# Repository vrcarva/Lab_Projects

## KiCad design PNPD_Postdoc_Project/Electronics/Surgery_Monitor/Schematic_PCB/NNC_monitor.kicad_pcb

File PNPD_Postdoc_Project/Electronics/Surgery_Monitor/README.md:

# Surgery Monitor
   
Project for monitoring heart rate and rectal temperature during surgery. In addition, the rectal temperature will be used as a control for the thermal blanket heating.
   
NNC / UFMG - since November 2018   

UPDATES:   

-----   

Add temperature code - 18/12/18 - 22:45

-----

Fixed interrupt for Temperature / Pulse measurement timer - 28/12/18 - 10:40 . 

-----

Add 5V RELAY for temperature control - 18/01/19 - 7:00 . 

--------------------------------------------------------------------------------

PULSE SENSOR:

References:

Guides:

   https://www.hackster.io/104829/detecting-heart-rate-with-a-photoresistor-680b58
   https://github.com/WorldFamousElectronics/PulseSensor_Amped_Arduino 
   https://makezine.com/projects/ir-pulse-sensor/
   https://www.instructables.com/id/Heart-rate-measuring-device-using-arduino/

Guide for default code:
Pulse Sensor Amped 1.5    by Joel Murphy and Yury Gitman  
  
   http://www.pulsesensor.com
   https://github.com/WorldFamousElectronics/PulseSensor_Amped_Arduino

Notes:
This code:
1) INPUT SIGNAL ANALOG PIN 0
2) Blinks an LED to User's Live Heartbeat   PIN 13
2) Fades an LED to User's Live HeartBeat    PIN 5
3) Determines BPM
4) Prints All of the Above to Serial

-----------------------------------------------------------------------------------------------------------

TEMPERATURE:

Original Articles:

   https://learn.adafruit.com/thermistor/using-a-thermistor

Other Guides:

   http://www.resistorguide.com/ntc-thermistor/
   https://en.wikipedia.org/wiki/Thermistor

Resistance at 25 degrees C --> // https://www.ametherm.com/blog/thermistor/arduino-and-thermistors

I have 2 kinds of Thermistors: 

- THERMISTOR NTC from TR-200 Temperaturregler Fine Science Tools - resistence 2252 ohm (25 C)
- THERMISTOR NTC 100K (25 C) from Filipe Flop store (Im using this one): 

   https://www.filipeflop.com/produto/termistor-ntc-100k-com-cabo/

Notes:
This code:
1) INPUT SIGNAL ANALOG PIN 1

--------------------------------------------------------------------------------

5V RELAY for temperature control

References:

Guides:
        
   http://www.circuitbasics.com/setting-up-a-5v-relay-on-the-arduino/
        
Notes:
This code:
1) OUTPUT SIGNAL DIGITAL PIN 2

--------------------------------------------------------------------------------
OLED DISPLAY:

Guides:
     
   https://startingelectronics.org/tutorials/arduino/modules/OLED-128x64-I2C-display/
   http://www.xtronical.com/pulseheartsensor/
   https://cdn-shop.adafruit.com/datasheets/SSD1306.pdf
   http://www.solomon-systech.com/files/ck/files/catalog/SSLcatalog_AD_OLED_Driver_IC_201604.pdf
   https://learn.adafruit.com/adafruit-gfx-graphics-library

Notes:
This code:

Arduino Uno/2009:

Display:  
SDA pin   -> Arduino Analog 4 or the dedicated SDA pin .     
SCL pin   -> Arduino Analog 5 or the dedicated SCL pin .

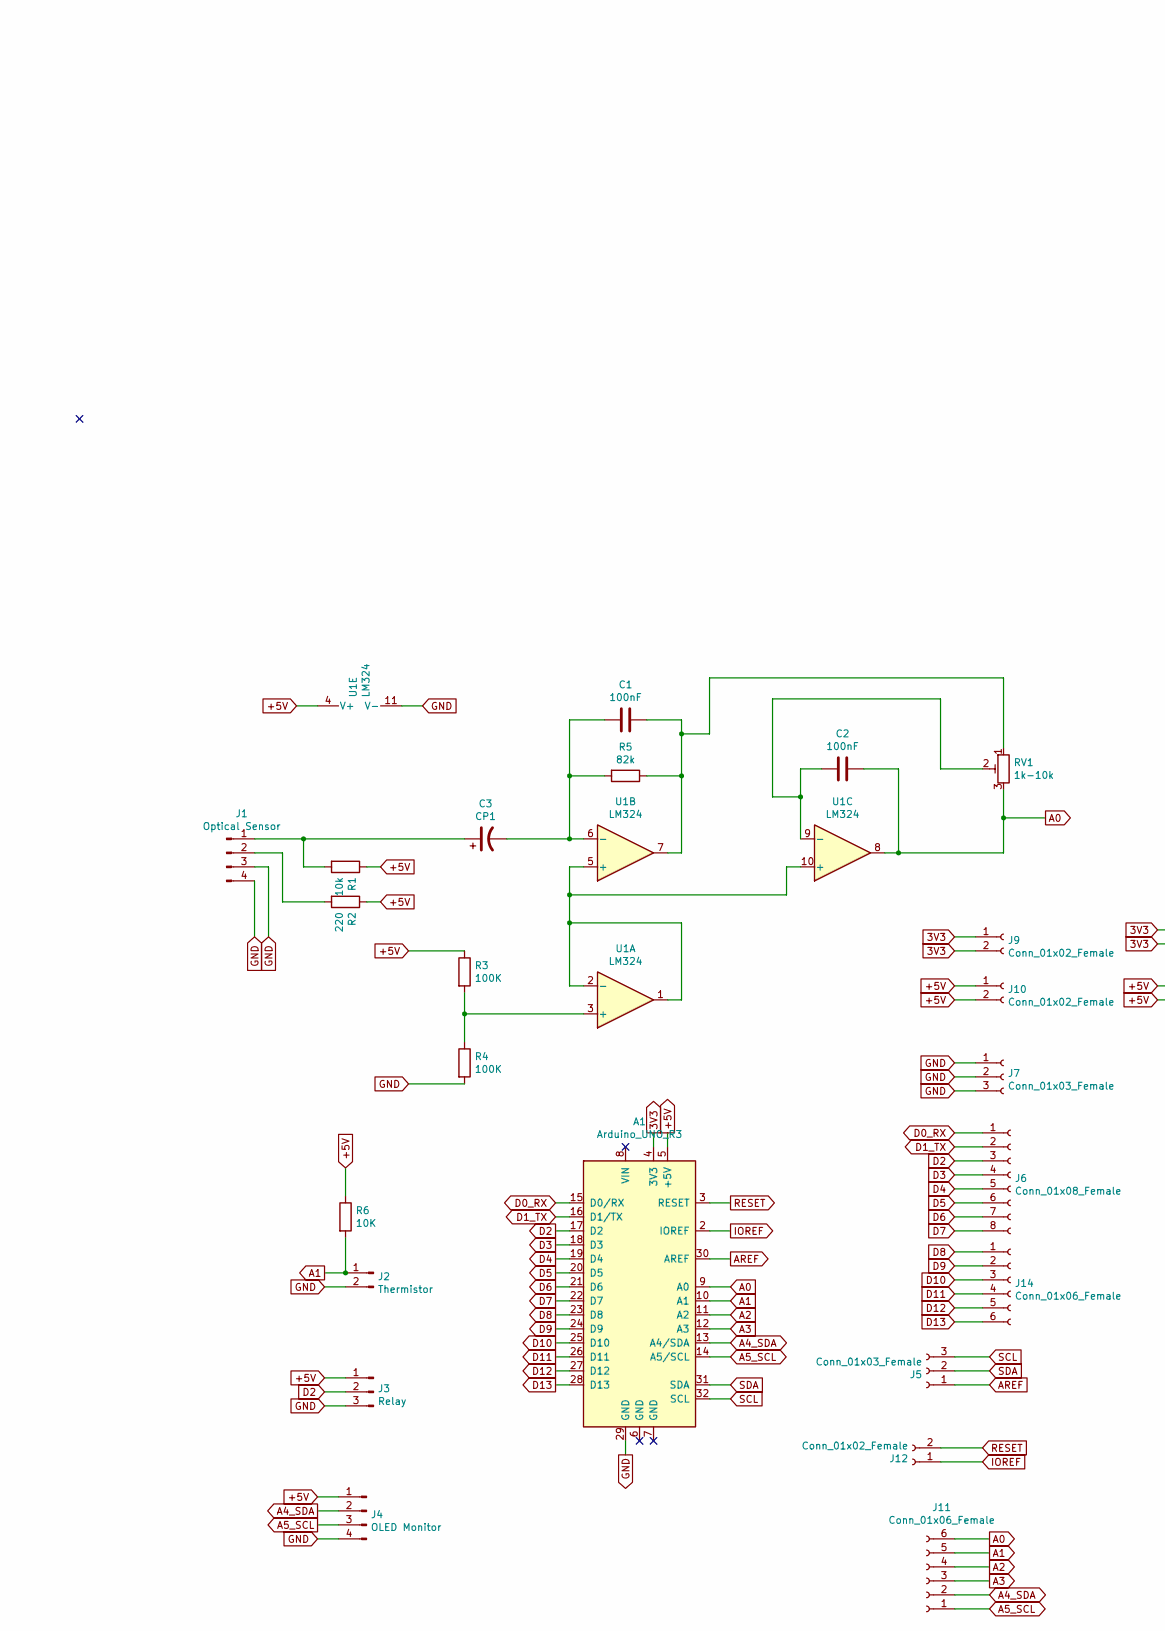
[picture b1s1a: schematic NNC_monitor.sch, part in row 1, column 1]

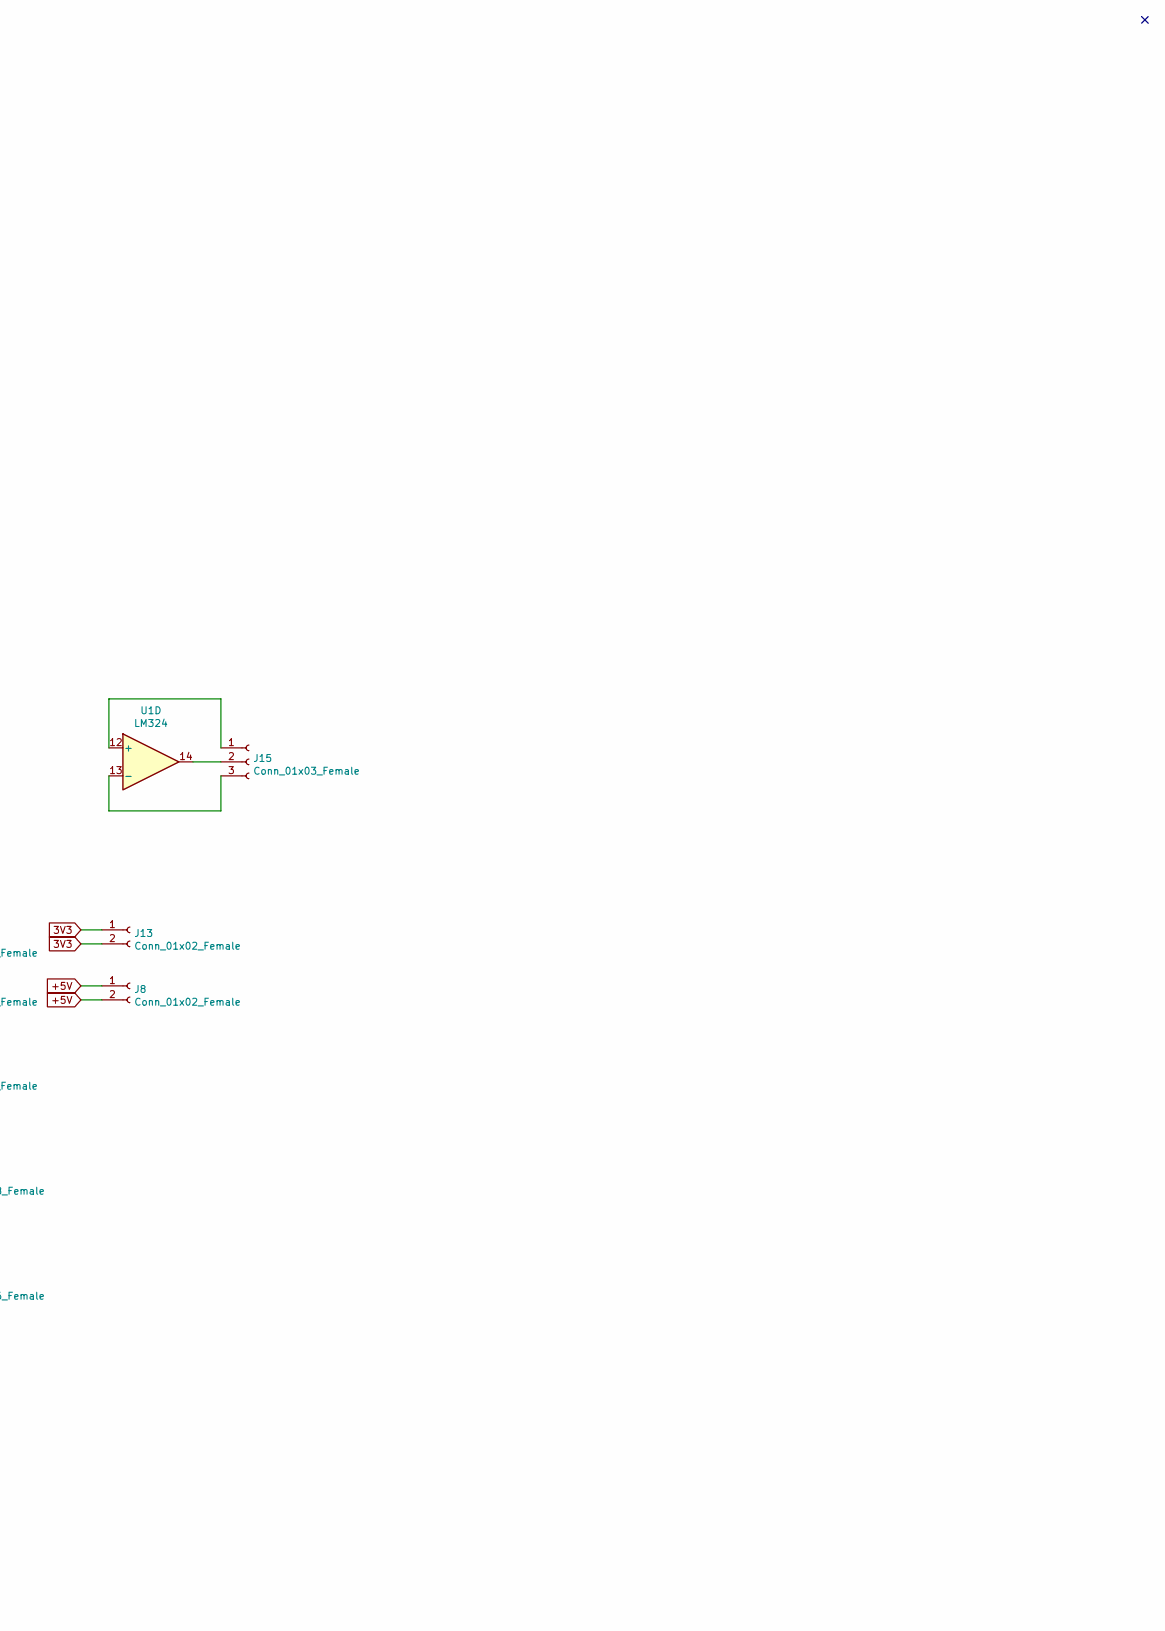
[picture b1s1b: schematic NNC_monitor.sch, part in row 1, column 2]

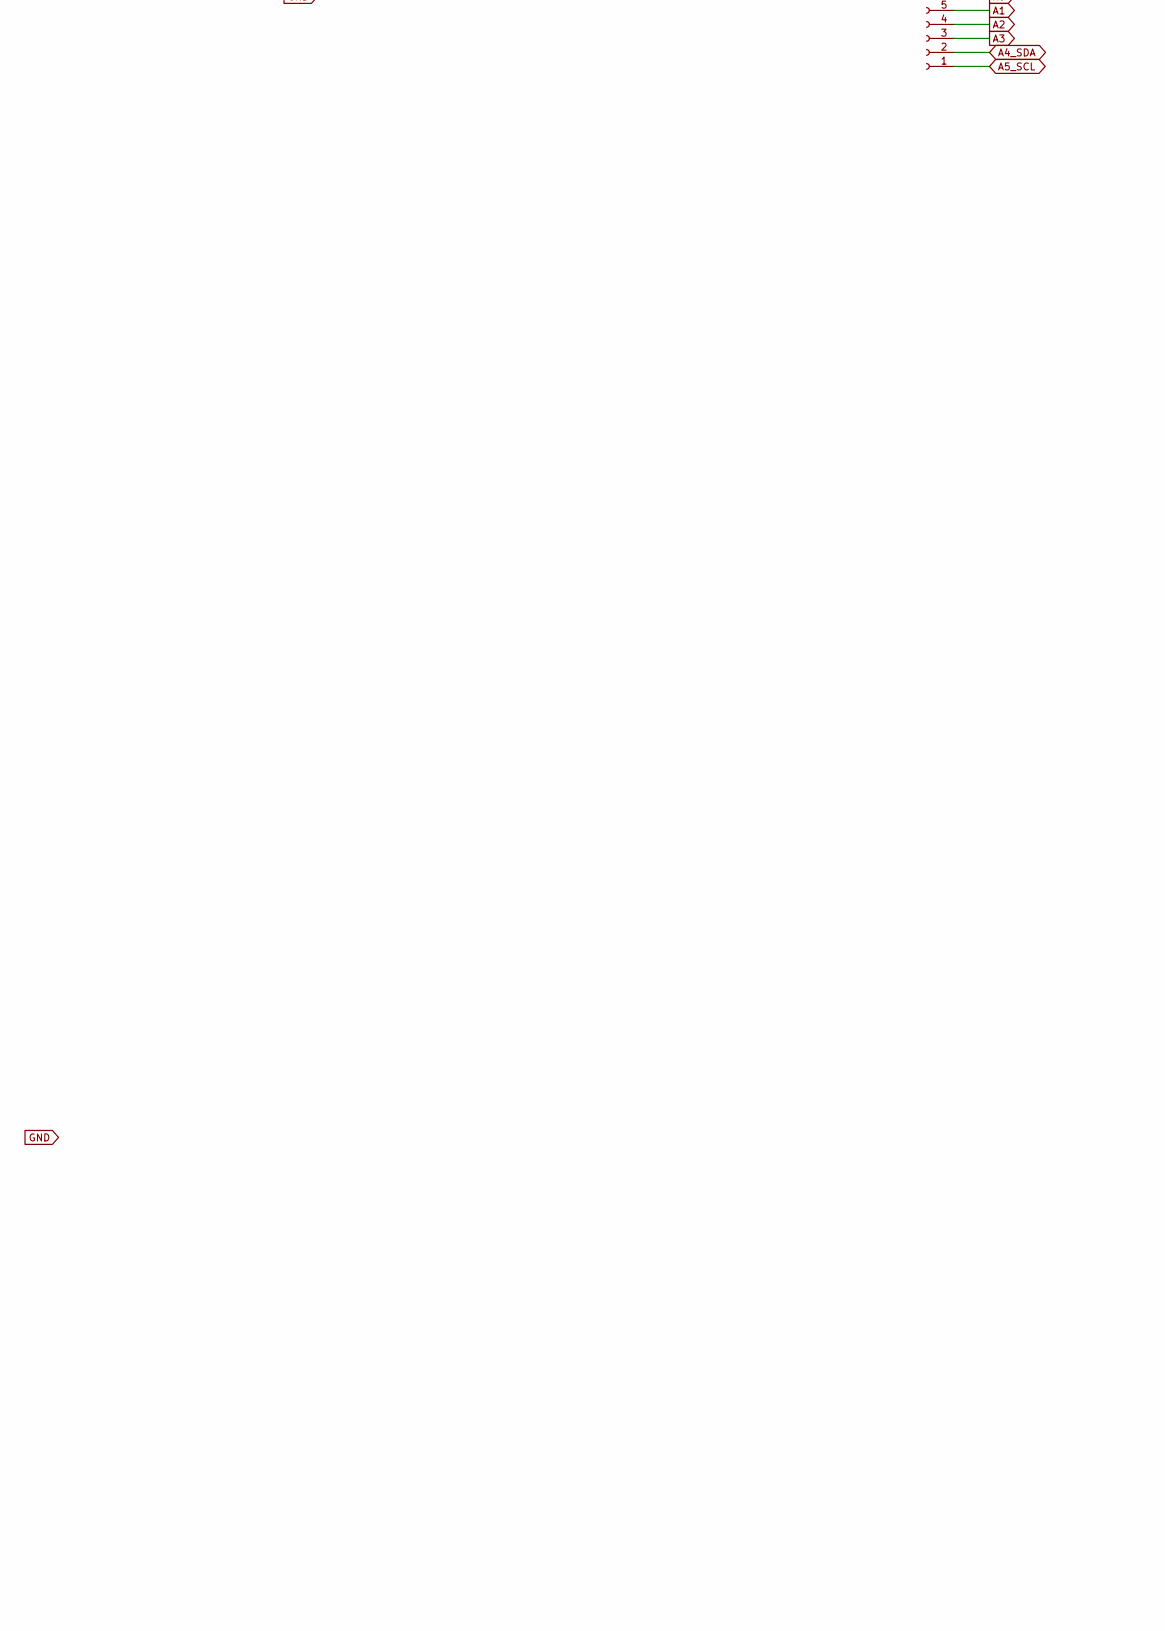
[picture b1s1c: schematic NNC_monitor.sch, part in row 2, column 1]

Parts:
A1: Arduino_UNO_R3
C1, C2: 100nF; C_Disc_D3_P2.5
C3: CP1; C_Radial_D5_L6_P2.5
J1: Optical Sensor; Molex_KK-254_AE-6410-04A_1x04_P2.54mm_Vertical
J2: Thermistor; Molex_KK-254_AE-6410-02A_1x02_P2.54mm_Vertical
J3: Relay; Molex_KK-254_AE-6410-03A_1x03_P2.54mm_Vertical
J4: OLED Monitor; Molex_KK-254_AE-6410-04A_1x04_P2.54mm_Vertical
J5, J7, J15: Conn_01x03_Female; PinSocket_1x03_P2.54mm_Vertical
J6: Conn_01x08_Female; PinSocket_1x08_P2.54mm_Vertical
J8, J9, J10, J12, J13: Conn_01x02_Female; PinSocket_1x02_P2.54mm_Vertical
J11, J14: Conn_01x06_Female; PinSocket_1x06_P2.54mm_Vertical
R1: 10k; Resistor_Horizontal_RM10mm
R2: 220; Resistor_Horizontal_RM10mm
R3, R4: 100K; Resistor_Horizontal_RM10mm
R5: 82k; Resistor_Horizontal_RM10mm
R6: 10K; Resistor_Horizontal_RM10mm
RV1: 1k-10k; Potentiometer_Trimmer-Suntan-TSR-3386P
U1: LM324; DIP-14_W7.62mm

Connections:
3V3: A1.4 (3V3), J9.1, J9.2, J13.1, J13.2
+5V: A1.5 (+5V), J3.1, J4.1, J8.1, J8.2, J10.1, J10.2, R1.1, R2.1, R3.1, R6.1, U1.4 (V+); also elsewhere on the board
A0: A1.9 (A0), C2.1, J11.6, RV1.3, U1.8
A1: A1.10 (A1), J2.1, J11.5, R6.2
A2: A1.11 (A2), J11.4
A3: A1.12 (A3), J11.3
A4_SDA: A1.13 (A4/SDA), J4.2, J11.2
A5_SCL: A1.14 (A5/SCL), J4.3, J11.1
AREF: A1.30 (AREF), J5.1
D0_RX: A1.15 (D0/RX), J6.1
D1_TX: A1.16 (D1/TX), J6.2
D2: A1.17 (D2), J3.2, J6.3
D3: A1.18 (D3), J6.4
D4: A1.19 (D4), J6.5
D5: A1.20 (D5), J6.6
D6: A1.21 (D6), J6.7
D7: A1.22 (D7), J6.8
D8: A1.23 (D8), J14.1
D9: A1.24 (D9), J14.2
D10: A1.25 (D10), J14.3
D11: A1.26 (D11), J14.4
D12: A1.27 (D12), J14.5
D13: A1.28 (D13), J14.6
GND: A1.29 (GND), J1.3, J1.4, J2.2, J3.3, J4.4, J7.1, J7.2, J7.3, R4.2, U1.11 (V-)
IOREF: A1.2 (IOREF), J12.1
unnamed: C1.1, R5.1, RV1.1, U1.7
unnamed: C1.2, C3.2, R5.2, U1.6 (-)
unnamed: C2.2, RV1.2, U1.9 (-)
unnamed: C3.1, J1.1, R1.2
unnamed: J1.2, R2.2
unnamed: J15.1, U1.12 (+)
unnamed: J15.2, U1.14
unnamed: J15.3, U1.13 (-)
unnamed: R3.2, R4.1, U1.3 (+)
unnamed: U1.1, U1.2 (-), U1.5 (+), U1.10 (+)
RESET: A1.3 (RESET), J12.2
SCL: A1.32 (SCL), J5.3
SDA: A1.31 (SDA), J5.2

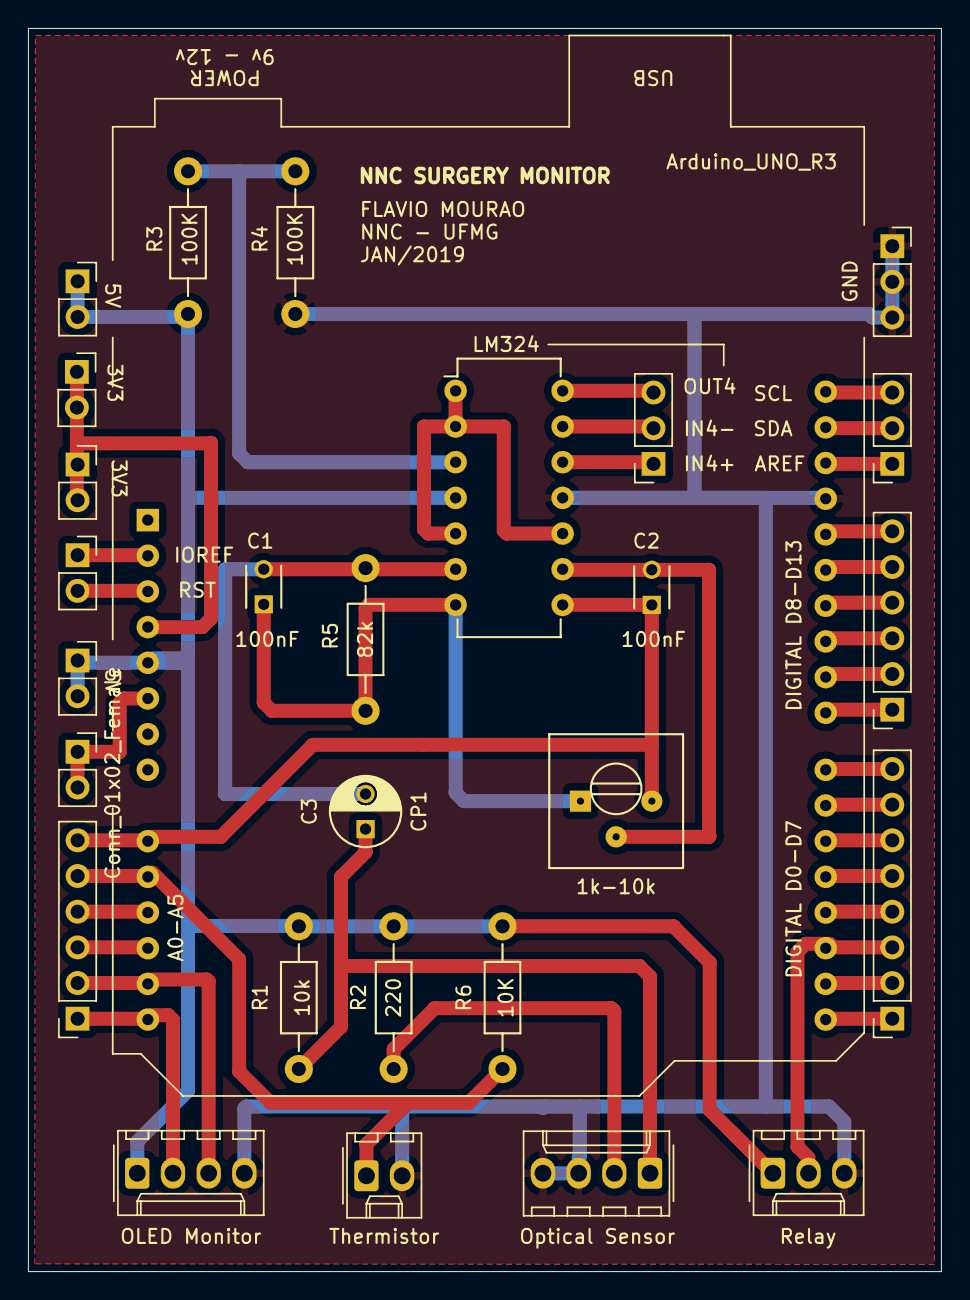
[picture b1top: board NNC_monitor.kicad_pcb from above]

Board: 2 copper layers, 65.0 x 88.5 mm, 28 parts (1 on the bottom side), 38 nets.

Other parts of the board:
J8#2: Conn_01x02_Female; PinSocket_1x02_P2.54mm_Vertical

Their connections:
+5V: J8#2.1, J8#2.2; also elsewhere on the board

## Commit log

2019-06-23 Update 23-06-19
2019-08-17 Update 17-08-19
2019-08-18 Updat 17-08-19
2019-08-19 Update 19-08-19
2019-08-19 Updat 19-08-19
2019-08-21 Update 21-08-19
2019-12-20 Update 20-12-19
2020-03-26 Update 26-03-2020
2020-03-31 update 31-03-20
2020-03-31 update 01-04-20
2020-04-01 update 01-04-2020
    add Short-time FFT matlab script
2020-04-02 update 02-04-20
2020-04-06 update 06-04-20
2020-04-08 update 07-04-20
2020-04-08 update 08-04-20
2020-04-10 Update 10-04-20
